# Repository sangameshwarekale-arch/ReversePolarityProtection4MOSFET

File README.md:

# 24 V / 25.2 V maximum /45 A target — routed evaluation, revision E

Open **ReversePolarityProtection4MOSFET.kicad_pro** in KiCad9. All CAD files are native/editable, with local symbol and footprint libraries and a matching .kicad_dru rules file. The PCB contains38 footprints,18 rear components,195 track segments,100 vias and14 filled zones. The original outline, fixed connectors and existing component values/connections are preserved.

**This is an engineering candidate, not qualified for45A operation or manufacture.** Final checks: ERC0; DRC0 errors and12 missing original-courtyard warnings;0 unconnected;0 schematic/PCB parity issues. No ignored DRC categories or exclusions hide those warnings.

Start with the [current routed review](redesign45A/routed/README.md), [comparison image](redesign45A/routed/images/routed-comparison.png), [calculation report](redesign45A/routed/calculations/routing-calculations.md), [check results](redesign45A/routed/reports/check-summary.md) and [BOM](BOM.csv). The [bottom-component list](redesign45A/placement/moved-to-bottom.csv) and [release holds](redesign45A/routed/changes-and-release-holds.md) are included.

The provisional four70um-copper stack, actual thermal performance, incoming/legacy termination ratings, M5 terminal stencil/hardware/support and special filled/capped via process require qualification. Balance connector paths remain intentionally open and unprotected; preserving the existing schematic does not implement balance-reversal protection. No manufacturing files are released.

The actual open source was C:/Users/sanga/Desktop/ReversePolarityProtection4MOSFET. Its77 files were backed up before modification; the untouched copy/manifest are in redesign45A/original-open-project-backup and original-open-project-sha256.json. The Desktop source is unchanged. Open this Documents/Codex project to see the routed version. Writing back to Desktop requires that folder to be in the writable workspace.

The earlier placement-only and60A studies remain historical snapshots on disk; the authoritative current material is redesign45A/routed. The routed ZIP includes native CAD, local libraries, BOM, current reports/images/calculations, approval record and source hash records; backup file folders remain on disk and are excluded from the ZIP. Optional KiCad stock3D models are not bundled. No actual Saturn results were obtained.

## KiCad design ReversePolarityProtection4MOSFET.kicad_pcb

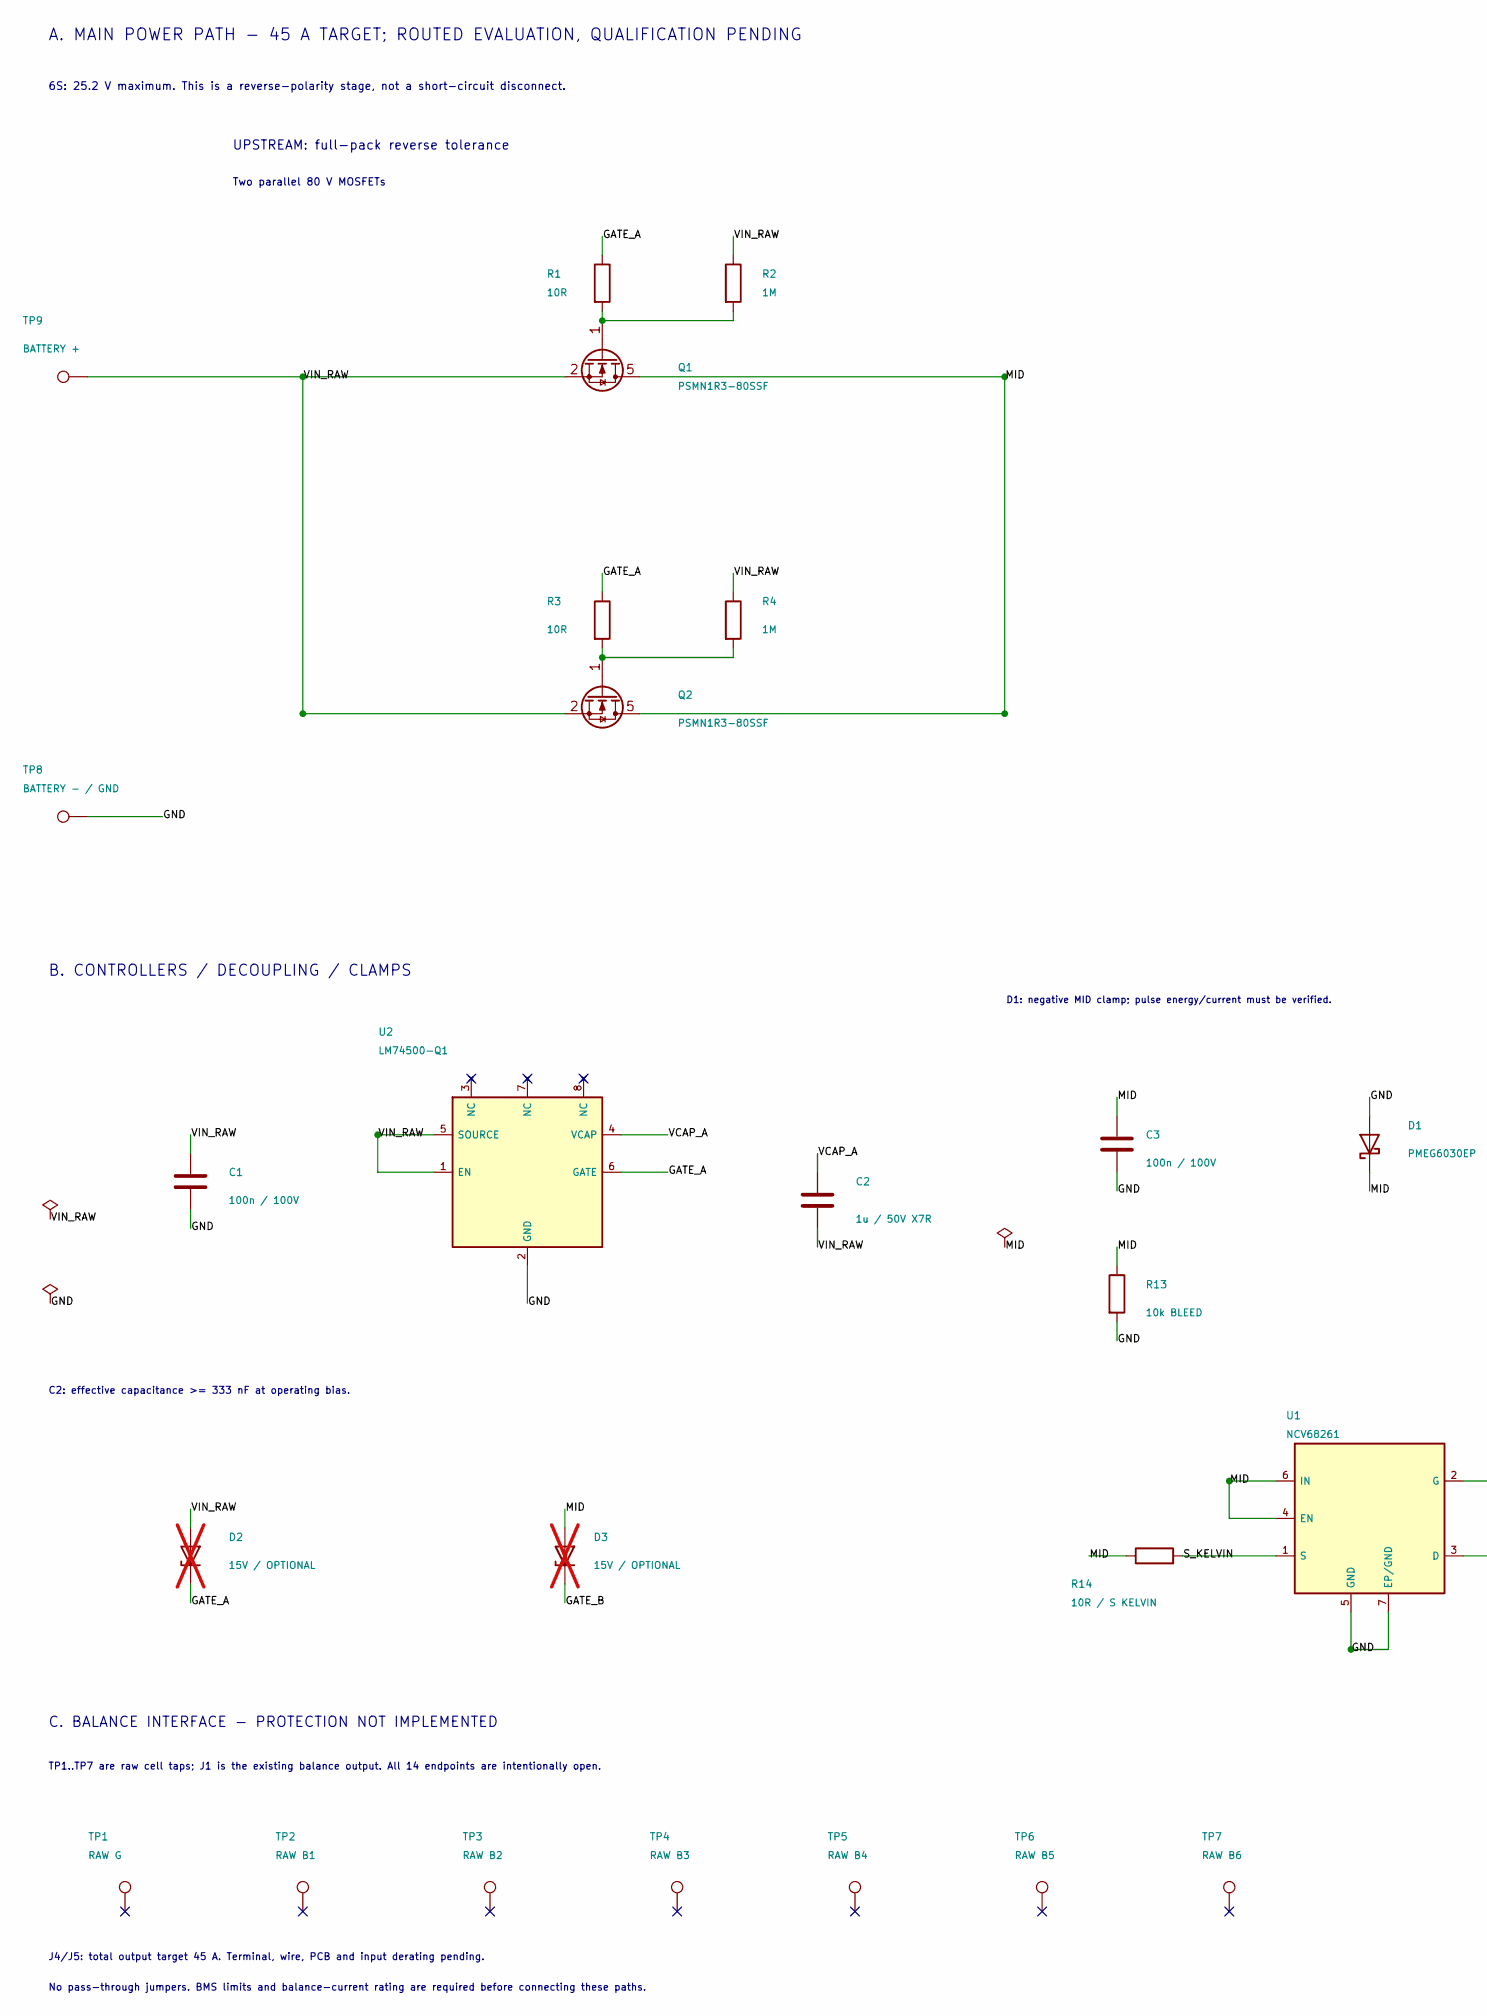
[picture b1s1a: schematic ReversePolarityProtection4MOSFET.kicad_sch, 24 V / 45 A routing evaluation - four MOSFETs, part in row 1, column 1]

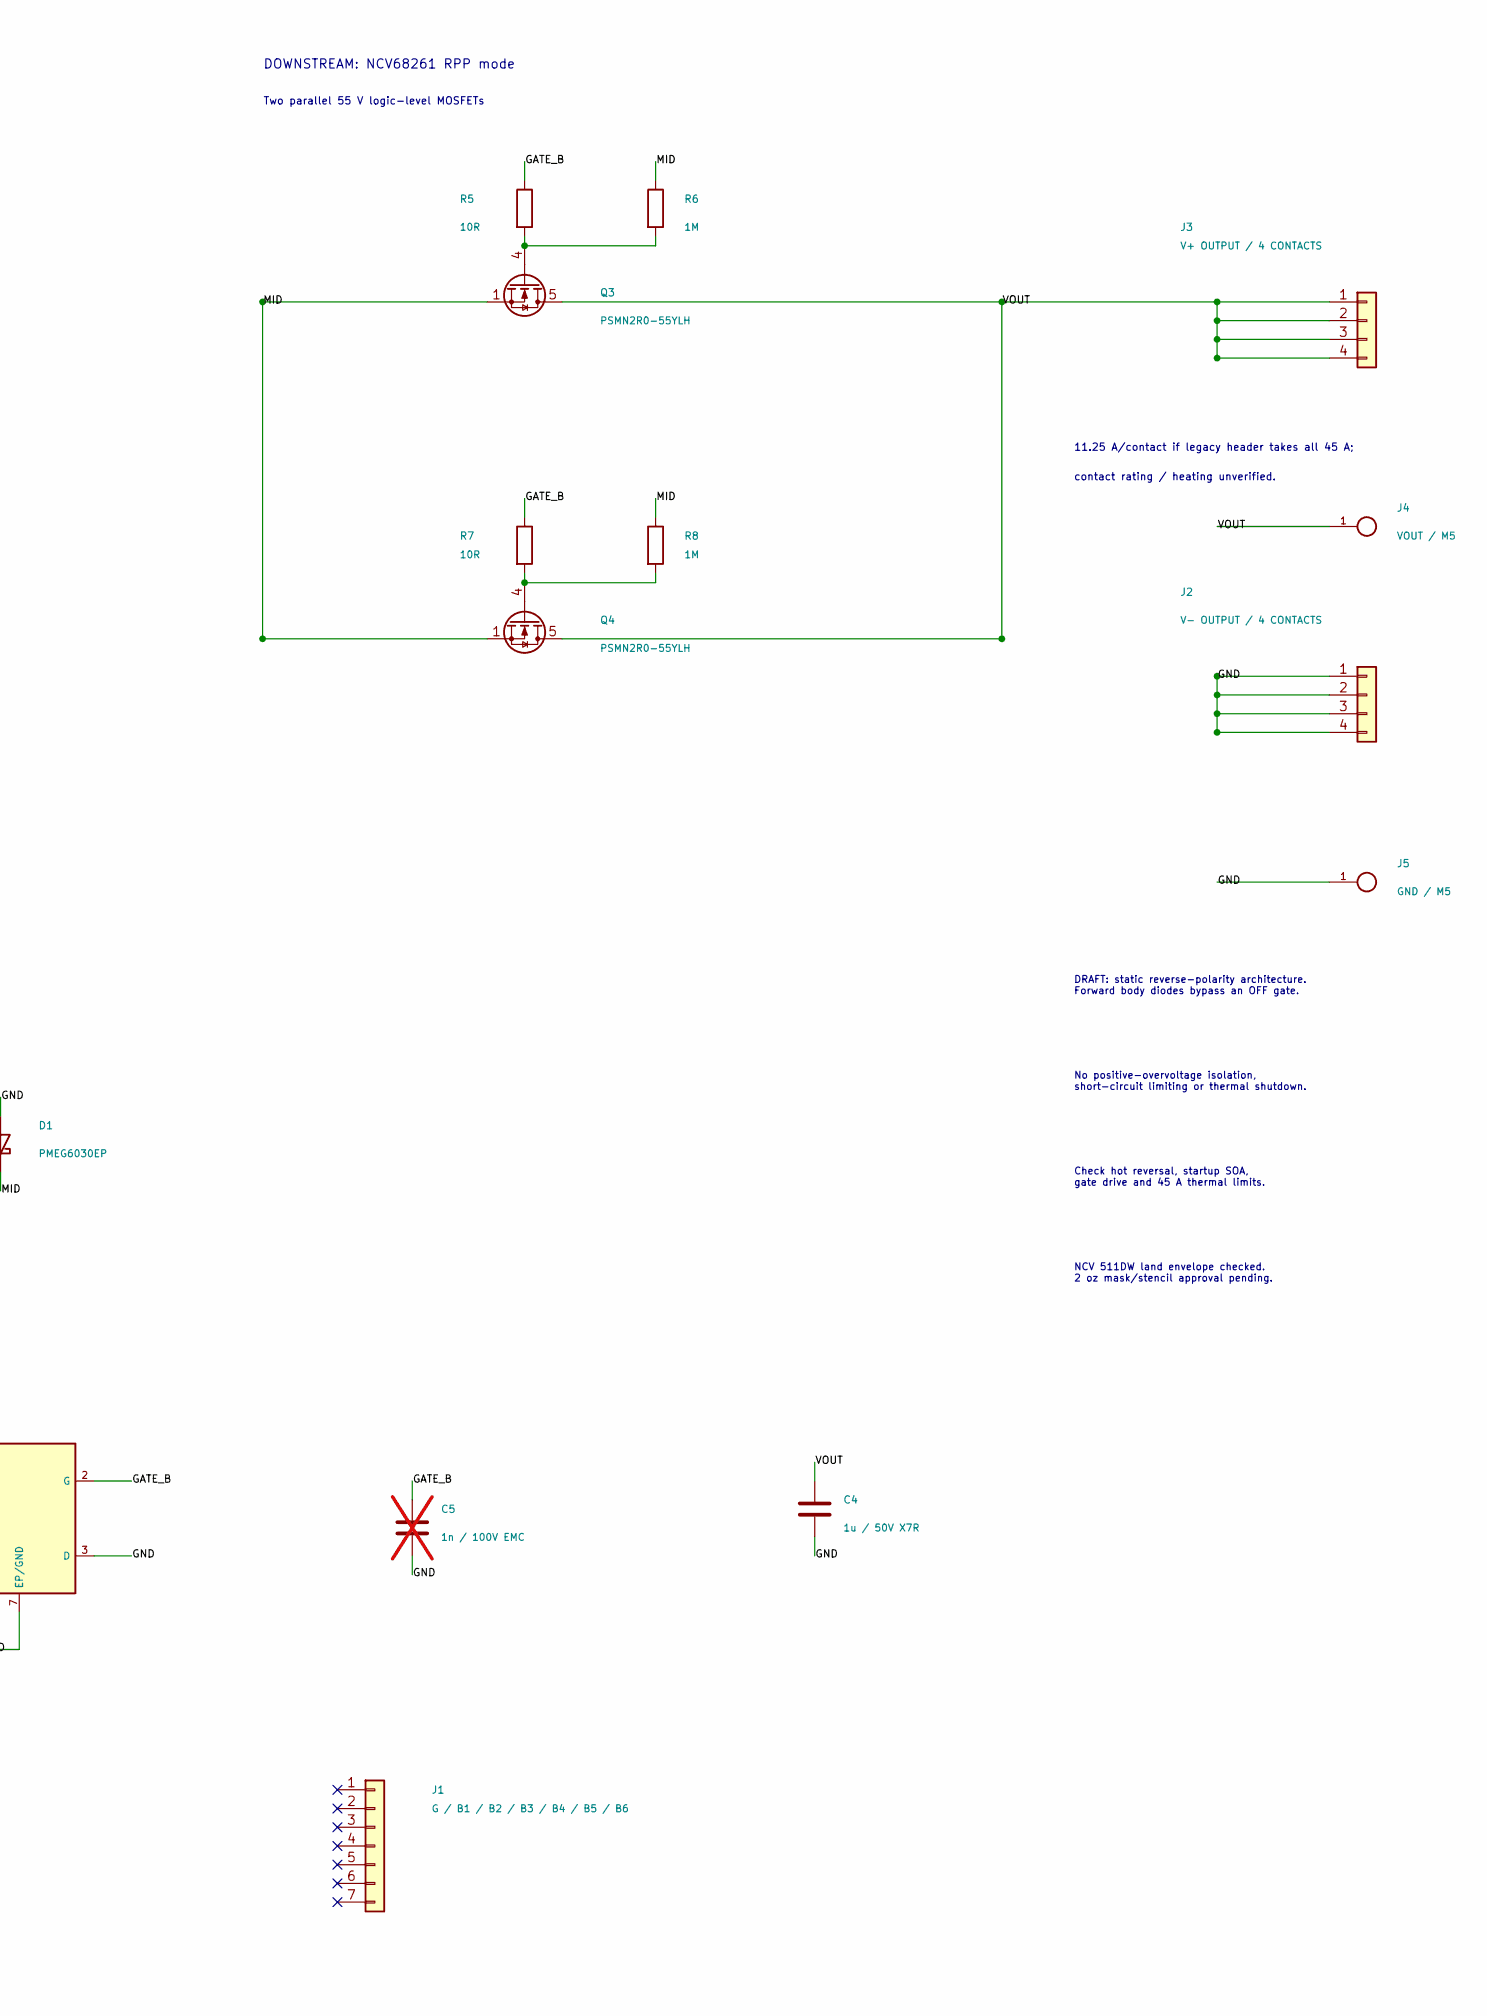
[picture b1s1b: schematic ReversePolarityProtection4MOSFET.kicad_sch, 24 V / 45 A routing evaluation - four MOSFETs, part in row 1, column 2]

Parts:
C1, C3: 100n / 100V; C_0603_1608Metric; MPN GRM188R72A104KA35D
C2, C4: 1u / 50V X7R; C_0805_2012Metric; MPN GCM21BR71H105KA03L
C5: 1n / 100V EMC; C_0603_1608Metric; MPN GCM1885C2A102JA16D; not fitted
D1: PMEG6030EP; SOD128; MPN PMEG6030EP,115
D2, D3: 15V / OPTIONAL; SOD123F; MPN BZT52H-C15,115; not fitted
J1: G / B1 / B2 / B3 / B4 / B5 / B6; Header_1x07_P2.50mm_DXF; MPN EXISTING CONNECTOR - RATING UNKNOWN
J2: V- OUTPUT / 4 CONTACTS; Connector_1x04_P2.50mm_VMinus_DXF; MPN EXISTING CONNECTOR - RATING UNKNOWN
J3: V+ OUTPUT / 4 CONTACTS; Connector_1x04_P2.50mm_VPlus_DXF; MPN EXISTING CONNECTOR - RATING UNKNOWN
J4: VOUT / M5; Wuerth_7466205R_M5_SMT; MPN 7466205R
J5: GND / M5; Wuerth_7466205R_M5_SMT; MPN 7466205R
Q1, Q2: PSMN1R3-80SSF; LFPAK88; MPN PSMN1R3-80SSFJ
Q3, Q4: PSMN2R0-55YLH; LFPAK56E; MPN PSMN2R0-55YLHX
R1, R3, R5, R7: 10R; R_0603_1608Metric; MPN RC0603FR-0710RL
R2, R4, R6, R8: 1M; R_0603_1608Metric; MPN RC0603FR-071ML
R13: 10k BLEED; R_0805_2012Metric; MPN RC0805FR-0710KL
R14: 10R / S KELVIN; R_0603_1608Metric; MPN RC0603FR-0710RL
TP1: RAW G; BatteryTap_G_DXF; MPN EXISTING TAP
TP2: RAW B1; BatteryTap_B1_DXF; MPN EXISTING TAP
TP3: RAW B2; BatteryTap_B2_DXF; MPN EXISTING TAP
TP4: RAW B3; BatteryTap_B3_DXF; MPN EXISTING TAP
TP5: RAW B4; BatteryTap_B4_DXF; MPN EXISTING TAP
TP6: RAW B5; BatteryTap_B5_DXF; MPN EXISTING TAP
TP7: RAW B6; BatteryTap_B6_DXF; MPN EXISTING TAP
TP8: BATTERY - / GND; WireSolderPad_VMinus_DXF; MPN EXISTING TERMINATION - RATING UNKNOWN
TP9: BATTERY +; WireSolderPad_VPlus_DXF; MPN EXISTING TERMINATION - RATING UNKNOWN
U1: NCV68261; NCV68261_WDFNW6; MPN NCV68261MTWAITBG
U2: LM74500-Q1; TI_DDF8; MPN LM74500QDDFRQ1

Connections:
/GATE_A: D2.1 (K), R1.1, R3.1, U2.6 (GATE)
/GATE_B: C5.1, D3.1 (K), R5.1, R7.1, U1.2 (G)
/GND: C1.2, C3.2, C4.2, C5.2, D1.2 (A), J2.1, J2.2, J2.3, J2.4, J5.1, R13.2, TP8.1, U1.3 (D), U1.5 (GND), U1.7 (EP/GND), U2.2 (GND)
/MID: C3.1, D1.1 (K), D3.2 (A), Q1.5 (D), Q2.5 (D), Q3.1 (S), Q3.2 (S), Q3.3 (S), Q4.1 (S), Q4.2 (S), Q4.3 (S), R6.1, R8.1, R13.1, R14.1, U1.4 (EN), U1.6 (IN)
/S_KELVIN: R14.2, U1.1 (S)
/VCAP_A: C2.1, U2.4 (VCAP)
/VIN_RAW: C1.1, C2.2, D2.2 (A), Q1.2 (S), Q1.3 (S), Q1.4 (S), Q2.2 (S), Q2.3 (S), Q2.4 (S), R2.1, R4.1, TP9.1, U2.1 (EN), U2.5 (SOURCE)
/VOUT: C4.1, J3.1, J3.2, J3.3, J3.4, J4.1, Q3.5 (D), Q4.5 (D)
unnamed: Q1.1 (G), R1.2, R2.2
unnamed: Q2.1 (G), R3.2, R4.2
unnamed: Q3.4 (G), R5.2, R6.2
unnamed: Q4.4 (G), R7.2, R8.2

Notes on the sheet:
A. MAIN POWER PATH - 45 A TARGET; ROUTED EVALUATION, QUALIFICATION PENDING
6S: 25.2 V maximum. This is a reverse-polarity stage, not a short-circuit disconnect.
UPSTREAM: full-pack reverse tolerance
DOWNSTREAM: NCV68261 RPP mode
Two parallel 80 V MOSFETs
Two parallel 55 V logic-level MOSFETs
11.25 A/contact if legacy header takes all 45 A;
contact rating / heating unverified.
B. CONTROLLERS / DECOUPLING / CLAMPS
C2: effective capacitance >= 333 nF at operating bias.
D1: negative MID clamp; pulse energy/current must be verified.
C. BALANCE INTERFACE - PROTECTION NOT IMPLEMENTED
TP1..TP7 are raw cell taps; J1 is the existing balance output. All 14 endpoints are intentionally open.
No pass-through jumpers. BMS limits and balance-current rating are required before connecting these paths.
DRAFT: static reverse-polarity architecture. Forward body diodes bypass an OFF gate.
No positive-overvoltage isolation, short-circuit limiting or thermal shutdown.
Check hot reversal, startup SOA, gate drive and 45 A thermal limits.
NCV 511DW land envelope checked. 2 oz mask/stencil approval pending.
J4/J5: total output target 45 A. Terminal, wire, PCB and input derating pending.

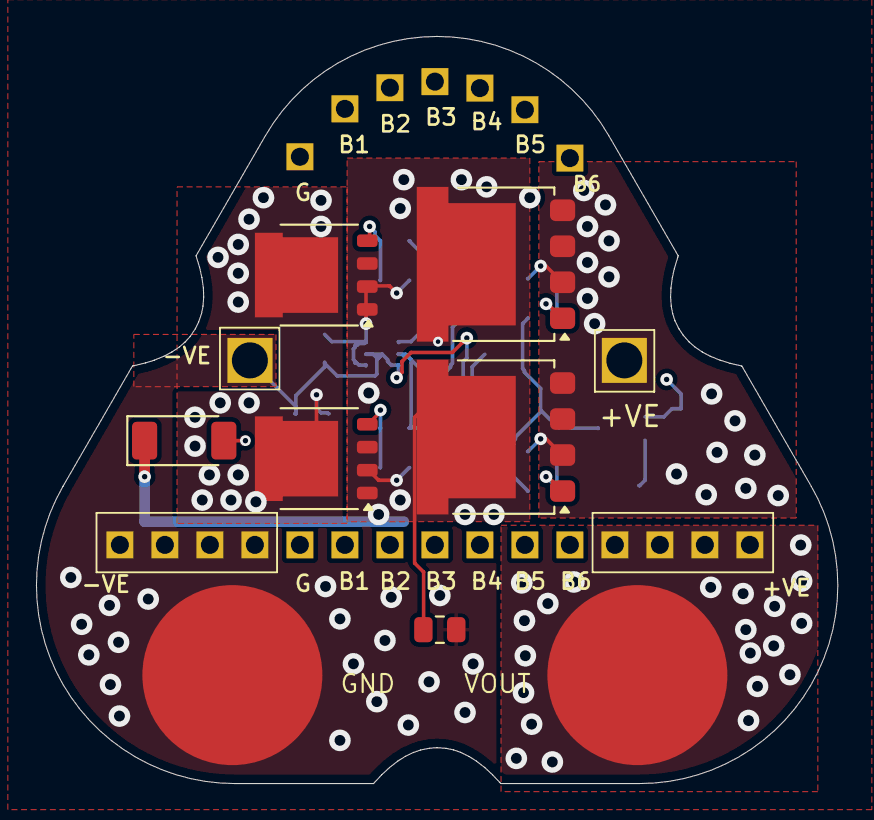
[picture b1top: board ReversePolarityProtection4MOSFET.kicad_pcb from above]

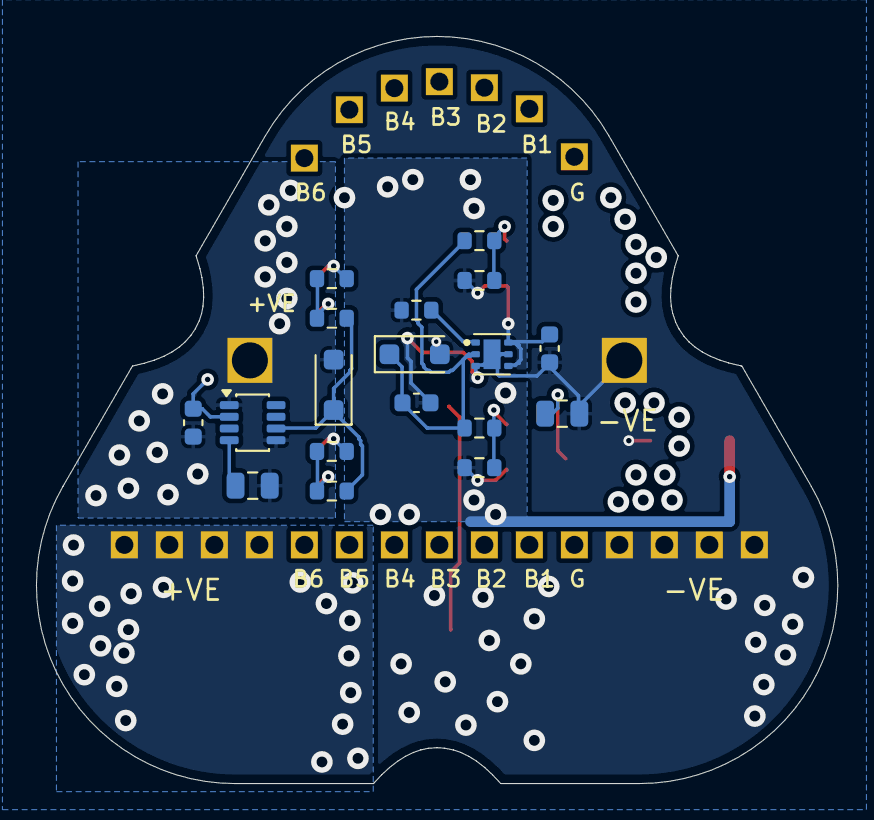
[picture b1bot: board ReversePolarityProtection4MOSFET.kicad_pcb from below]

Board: 4 copper layers, 44.5 x 41.5 mm, 38 parts (18 on the bottom side), 12 nets.

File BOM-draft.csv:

Reference,Value,Manufacturer part number,Footprint,Population,Datasheet
Q1,PSMN1R3-80SSF,PSMN1R3-80SSFJ,Protection:LFPAK88,Fit,https://assets.nexperia.com/documents/data-sheet/PSMN1R3-80SSF.pdf
R1,10R,RC0603FR-0710RL,Resistor_SMD:R_0603_1608Metric,Fit,~
R2,1M,RC0603FR-071ML,Resistor_SMD:R_0603_1608Metric,Fit,~
Q2,PSMN1R3-80SSF,PSMN1R3-80SSFJ,Protection:LFPAK88,Fit,https://assets.nexperia.com/documents/data-sheet/PSMN1R3-80SSF.pdf
R3,10R,RC0603FR-0710RL,Resistor_SMD:R_0603_1608Metric,Fit,~
R4,1M,RC0603FR-071ML,Resistor_SMD:R_0603_1608Metric,Fit,~
Q3,PSMN2R0-55YLH,PSMN2R0-55YLHX,Protection:LFPAK56E,Fit,https://assets.nexperia.com/documents/data-sheet/PSMN2R0-55YLH.pdf
R5,10R,RC0603FR-0710RL,Resistor_SMD:R_0603_1608Metric,Fit,~
R6,1M,RC0603FR-071ML,Resistor_SMD:R_0603_1608Metric,Fit,~
Q4,PSMN2R0-55YLH,PSMN2R0-55YLHX,Protection:LFPAK56E,Fit,https://assets.nexperia.com/documents/data-sheet/PSMN2R0-55YLH.pdf
R7,10R,RC0603FR-0710RL,Resistor_SMD:R_0603_1608Metric,Fit,~
R8,1M,RC0603FR-071ML,Resistor_SMD:R_0603_1608Metric,Fit,~
TP9,BATTERY +,EXISTING TERMINATION - RATING UNKNOWN,OriginalMechanical:WireSolderPad_VPlus_DXF,Fit,~
TP8,BATTERY - / GND,EXISTING TERMINATION - RATING UNKNOWN,OriginalMechanical:WireSolderPad_VMinus_DXF,Fit,~
J3,V+ OUTPUT / 4 CONTACTS,EXISTING CONNECTOR - RATING UNKNOWN,OriginalMechanical:Connector_1x04_P2.50mm_VPlus_DXF,Fit,~
J2,V- OUTPUT / 4 CONTACTS,EXISTING CONNECTOR - RATING UNKNOWN,OriginalMechanical:Connector_1x04_P2.50mm_VMinus_DXF,Fit,~
U2,LM74500-Q1,LM74500QDDFRQ1,Protection:TI_DDF8,Fit,https://www.ti.com/lit/ds/symlink/lm74500-q1.pdf
U1,NCV68261,NCV68261MTWAITBG,Protection:NCV68261_WDFNW6,Fit,https://www.onsemi.com/pdf/datasheet/ncv68261-d.pdf
R14,10R / S KELVIN,RC0603FR-0710RL,Resistor_SMD:R_0603_1608Metric,Fit,~
C1,100n / 100V,GRM188R72A104KA35D,Capacitor_SMD:C_0603_1608Metric,Fit,https://search.murata.co.jp/Ceramy/image/img/A01X/G101/ENG/G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
C2,1u / 50V X7R,GCM21BR71H105KA03L,Capacitor_SMD:C_0805_2012Metric,Fit,https://search.murata.co.jp/Ceramy/image/img/A01X/G101/ENG/G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
C3,100n / 100V,GRM188R72A104KA35D,Capacitor_SMD:C_0603_1608Metric,Fit,~
C4,1u / 50V X7R,GCM21BR71H105KA03L,Capacitor_SMD:C_0805_2012Metric,Fit,~
C5,1n / 100V EMC,GCM1885C2A102JA16D,Capacitor_SMD:C_0603_1608Metric,DNP,~
R13,10k BLEED,RC0805FR-0710KL,Resistor_SMD:R_0805_2012Metric,Fit,~
D1,PMEG6030EP,"PMEG6030EP,115",Protection:SOD128,Fit,https://assets.nexperia.com/documents/data-sheet/PMEG6030EP.pdf
D2,15V / OPTIONAL,"BZT52H-C15,115",Protection:SOD123F,DNP,https://assets.nexperia.com/documents/data-sheet/BZT52H_SER.pdf
D3,15V / OPTIONAL,"BZT52H-C15,115",Protection:SOD123F,DNP,https://assets.nexperia.com/documents/data-sheet/BZT52H_SER.pdf
TP1,RAW G,EXISTING TAP,OriginalMechanical:BatteryTap_G_DXF,Fit,~
TP2,RAW B1,EXISTING TAP,OriginalMechanical:BatteryTap_B1_DXF,Fit,~
TP3,RAW B2,EXISTING TAP,OriginalMechanical:BatteryTap_B2_DXF,Fit,~
TP4,RAW B3,EXISTING TAP,OriginalMechanical:BatteryTap_B3_DXF,Fit,~
TP5,RAW B4,EXISTING TAP,OriginalMechanical:BatteryTap_B4_DXF,Fit,~
TP6,RAW B5,EXISTING TAP,OriginalMechanical:BatteryTap_B5_DXF,Fit,~
TP7,RAW B6,EXISTING TAP,OriginalMechanical:BatteryTap_B6_DXF,Fit,~
J1,G / B1 / B2 / B3 / B4 / B5 / B6,EXISTING CONNECTOR - RATING UNKNOWN,OriginalMechanical:Header_1x07_P2.50mm_DXF,Fit,~
J4,VOUT / M5,7466205R,Protection:Wuerth_7466205R_M5_SMT,Candidate fit; thermal/mechanical/stencil qualification pending,https://www.we-online.com/components/products/datasheet/7466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
J5,GND / M5,7466205R,Protection:Wuerth_7466205R_M5_SMT,Candidate fit; thermal/mechanical/stencil qualification pending,https://www.we-online.com/components/products/datasheet/7466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
